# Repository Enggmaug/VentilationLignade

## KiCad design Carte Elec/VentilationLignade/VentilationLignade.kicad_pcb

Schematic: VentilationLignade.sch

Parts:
C1, C2, C3: 0.1uF; C_Rect_L7_W2.5_P5
C4, C5, C6, C7: 1uF; C_Radial_D8_L11.5_P3.5
P1: RelaisBoard1; Pin_Header_Straight_1x04
P2: PUIT_CAN; bornier2
P3: RelaisBoard2; Pin_Header_Straight_1x04
P4: TEMP_EXT; bornier2
P5: RelaisBoard3; Pin_Header_Straight_1x04
P6: TEMP_INT; bornier2
P7: RelaisBoard4; Pin_Header_Straight_1x04
P8: RelaisBoard5; Pin_Header_Straight_1x04
P9: TFT; Pin_Header_Straight_1x09
P10: SDCard; Pin_Header_Straight_1x05
P11: Codeur Rotatif; Pin_Header_Straight_1x05
P12: Teensy Bottom; Pin_Header_Straight_1x10
P13: EndStops1; bornier2
P14: Teensy_Haut; Pin_Header_Straight_1x13
P15: EndStops2; bornier2
P16: Teensy_cote; Pin_Header_Straight_1x07
P17: Retour 12V; bornier2
P18: Masse_12V; Pin_Header_Straight_1x04
P19, P20: CONN_01X03; Alim
P21: 12V_1et2; bornier2
P22: Teensy_Bas; Pin_Header_Straight_1x13
P23: Serial; Pin_Header_Straight_1x04
P24: CHEMINEE; bornier2
P25: RT_CLK1; Pin_Header_Straight_1x04
P26: RT_CLK2; Pin_Header_Straight_1x04
P27, P28, P29, P30: CONN_1; VIS
R1: R; Resistor_Horizontal_RM15mm
R2, R24, R26, R28: 4.47K; R_1206_HandSoldering
R3, R25, R27, R29: 91K; R_1206_HandSoldering
R30: 100K; R_1206_HandSoldering
RV1, RV2, RV3, RV4: 10K; Potar
SW2: BackLight_On/ff; Pin_Header_Straight_1x03

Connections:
12V1: P19.1, P21.1
12V1_ON: P7.3, P22.8
12V2: P20.1, P21.2 (PM)
12V2_ON: P8.3, P12.9
12V_CHECK: P14.1; also elsewhere on the board
+3.3V: C4.2, C5.2, C6.2, C7.2, P2.1, P4.1, P6.1, P9.1, P11.4, P14.11, P24.1, P25.3, R30.2; also elsewhere on the board
+5V: P1.4, P3.4, P5.4, P7.4, P8.4, P14.13, P23.4, SW2.1
/Optocouplers/12V_IN: P17.2 (PM); also elsewhere on the board
/Optocouplers/END_1_1: P13.2 (PM); also elsewhere on the board
/Optocouplers/END_1_2: P13.1; also elsewhere on the board
/Optocouplers/END_2_1: P15.2 (PM); also elsewhere on the board
/Optocouplers/END_2_2: P15.1; also elsewhere on the board
AGND: P14.12, RV1.1, RV2.1, RV3.1, RV4.1
BYPASS_1_F: P1.3, P22.2
BYPASS_1_O: P1.2, P22.3
BYPASS_2_F: P3.3, P22.4
BYPASS_2_O: P3.2, P22.5
ENCODEUR_A: C1.1, P11.1, P12.2
ENCODEUR_B: C2.1, P11.2, P12.3
ENCODEUR_SW: C3.1, P11.3, P12.4
ENDSTOP_1_1: P14.6; also elsewhere on the board
ENDSTOP_1_2: P14.5; also elsewhere on the board
ENDSTOP_2_1: P14.4; also elsewhere on the board
ENDSTOP_2_2: P14.3; also elsewhere on the board
GND: C1.2, C2.2, C3.2, P1.1, P3.1, P5.1, P7.1, P8.1, P9.2, P11.5, P16.4, P22.1, P23.1, P25.1, P25.2; also elsewhere on the board
GNDPWR: P17.1, P18.1, P18.2, P18.3, P18.4, P19.2, P19.3, P20.2, P20.3; also elsewhere on the board
unnamed: P9.4, R30.1
unnamed: P9.8, R1.1
unnamed: R1.2, SW2.2
unnamed: R2.2, R3.1
unnamed: R3.2, RV1.2, RV1.3
unnamed: R24.2, R25.1
unnamed: R25.2, RV2.2, RV2.3
unnamed: R26.2, R27.1
unnamed: R27.2, RV3.2, RV3.3
unnamed: R28.2, R29.1
unnamed: R29.2, RV4.2, RV4.3
RTCLK_CS: P22.11, P26.4
RTCLK_INTERRUPT: P22.10, P25.4
RX: P12.5, P23.2
SD_CS: P10.1, P14.2
SELECT_12V: P8.2, P12.1
SELECT_VMC: P7.2, P22.9
SPI_MISO: P9.9, P10.4, P16.1, P26.2
SPI_MOSI: P9.6, P10.2, P22.13, P26.3
SPI_SCK: P9.7, P10.3, P16.7, P26.1
TCHEM_AN: C7.1, P14.10, P24.2 (PM), R28.1
TEXT_AN: C5.1, P4.2 (PM), P14.8, R24.1
TFT_CS: P9.3, P22.12
TFT_DC: P9.5, P12.10
TFT_ONOFF: P12.8, SW2.3
TINT_AN: C6.1, P6.2 (PM), P14.7, R26.1
TPUIT_AN: C4.1, P2.2 (PM), P14.9, R2.1
TX: P12.6, P23.3
VENT_CAVE: P5.3, P22.6
VENT_CHEMINEE: P5.2, P22.7

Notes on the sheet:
Vis
VERS RELAIS
Entrées 12V
Vers RELAIS
CODEUR ROTATIF
ECRAN TFT
FINS DE COURSE BYPASS
TEENSY 3.1
RETOUR 12V
POWER FLAGS
REAL TIME CLOCK

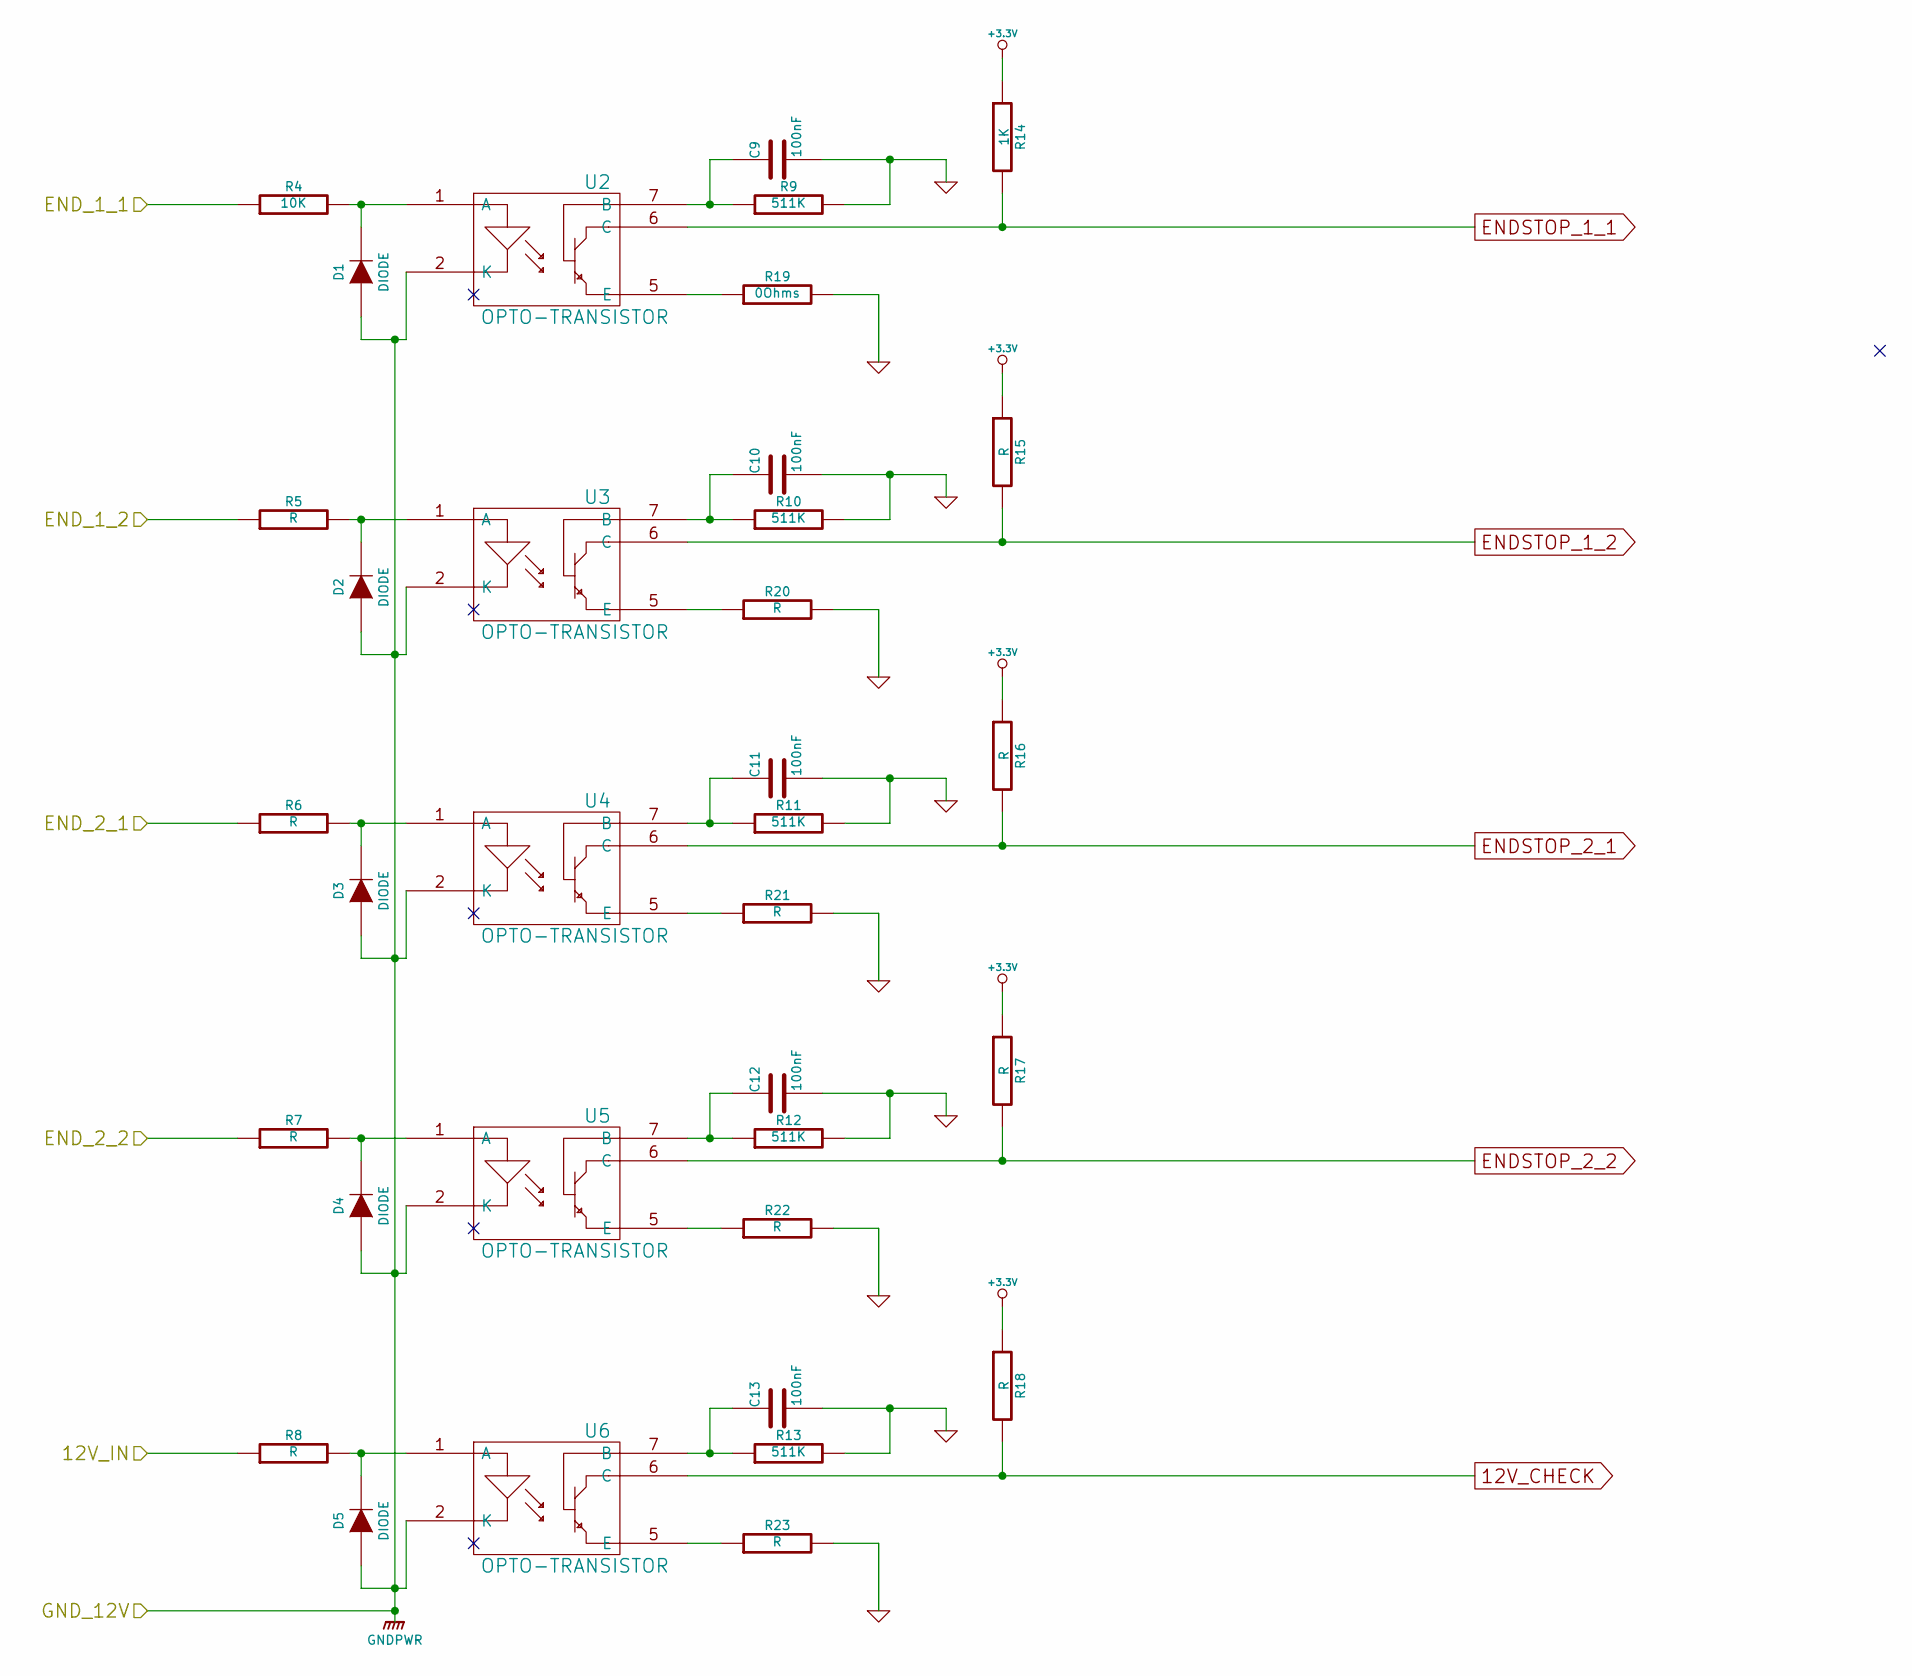
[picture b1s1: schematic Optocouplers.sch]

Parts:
C9, C10, C11, C12, C13: 100nF; C_0805_HandSoldering
D1, D2, D3, D4, D5: DIODE; SOT-23
R4: 10K; R_1206_HandSoldering
R5, R6, R7, R8, R15, R16, R17, R18, R20, R21, R22, R23: R; R_1206_HandSoldering
R9, R10, R11, R12, R13: 511K; R_1206_HandSoldering
R14: 1K; R_1206_HandSoldering
R19: 0Ohms; R_1206_HandSoldering
U2, U3, U4, U5, U6: OPTO-TRANSISTOR; SOIC-8-N

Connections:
12V_CHECK: R18.2, U6.6 (C); also elsewhere on the board
+3.3V: R14.1, R15.1, R16.1, R17.1, R18.1; also elsewhere on the board
/Optocouplers/12V_IN: R8.1; also elsewhere on the board
/Optocouplers/END_1_1: R4.1; also elsewhere on the board
/Optocouplers/END_1_2: R5.1; also elsewhere on the board
/Optocouplers/END_2_1: R6.1; also elsewhere on the board
/Optocouplers/END_2_2: R7.1; also elsewhere on the board
ENDSTOP_1_1: R14.2, U2.6 (C); also elsewhere on the board
ENDSTOP_1_2: R15.2, U3.6 (C); also elsewhere on the board
ENDSTOP_2_1: R16.2, U4.6 (C); also elsewhere on the board
ENDSTOP_2_2: R17.2, U5.6 (C); also elsewhere on the board
GND: C9.2, C10.2, C11.2, C12.2, C13.2, R9.2, R10.2, R11.2, R12.2, R13.2, R19.2, R20.2, R21.2, R22.2, R23.2; also elsewhere on the board
GNDPWR: D1.1 (A), D2.1 (A), D3.1 (A), D4.1 (A), D5.1 (A), U2.2 (K), U3.2 (K), U4.2 (K), U5.2 (K), U6.2 (K); also elsewhere on the board
unnamed: C9.1, R9.1, U2.7 (B)
unnamed: C10.1, R10.1, U3.7 (B)
unnamed: C11.1, R11.1, U4.7 (B)
unnamed: C12.1, R12.1, U5.7 (B)
unnamed: C13.1, R13.1, U6.7 (B)
unnamed: D1.2 (K), R4.2, U2.1 (A)
unnamed: D2.2 (K), R5.2, U3.1 (A)
unnamed: D3.2 (K), R6.2, U4.1 (A)
unnamed: D4.2 (K), R7.2, U5.1 (A)
unnamed: D5.2 (K), R8.2, U6.1 (A)
unnamed: R19.1, U2.5 (E)
unnamed: R20.1, U3.5 (E)
unnamed: R21.1, U4.5 (E)
unnamed: R22.1, U5.5 (E)
unnamed: R23.1, U6.5 (E)

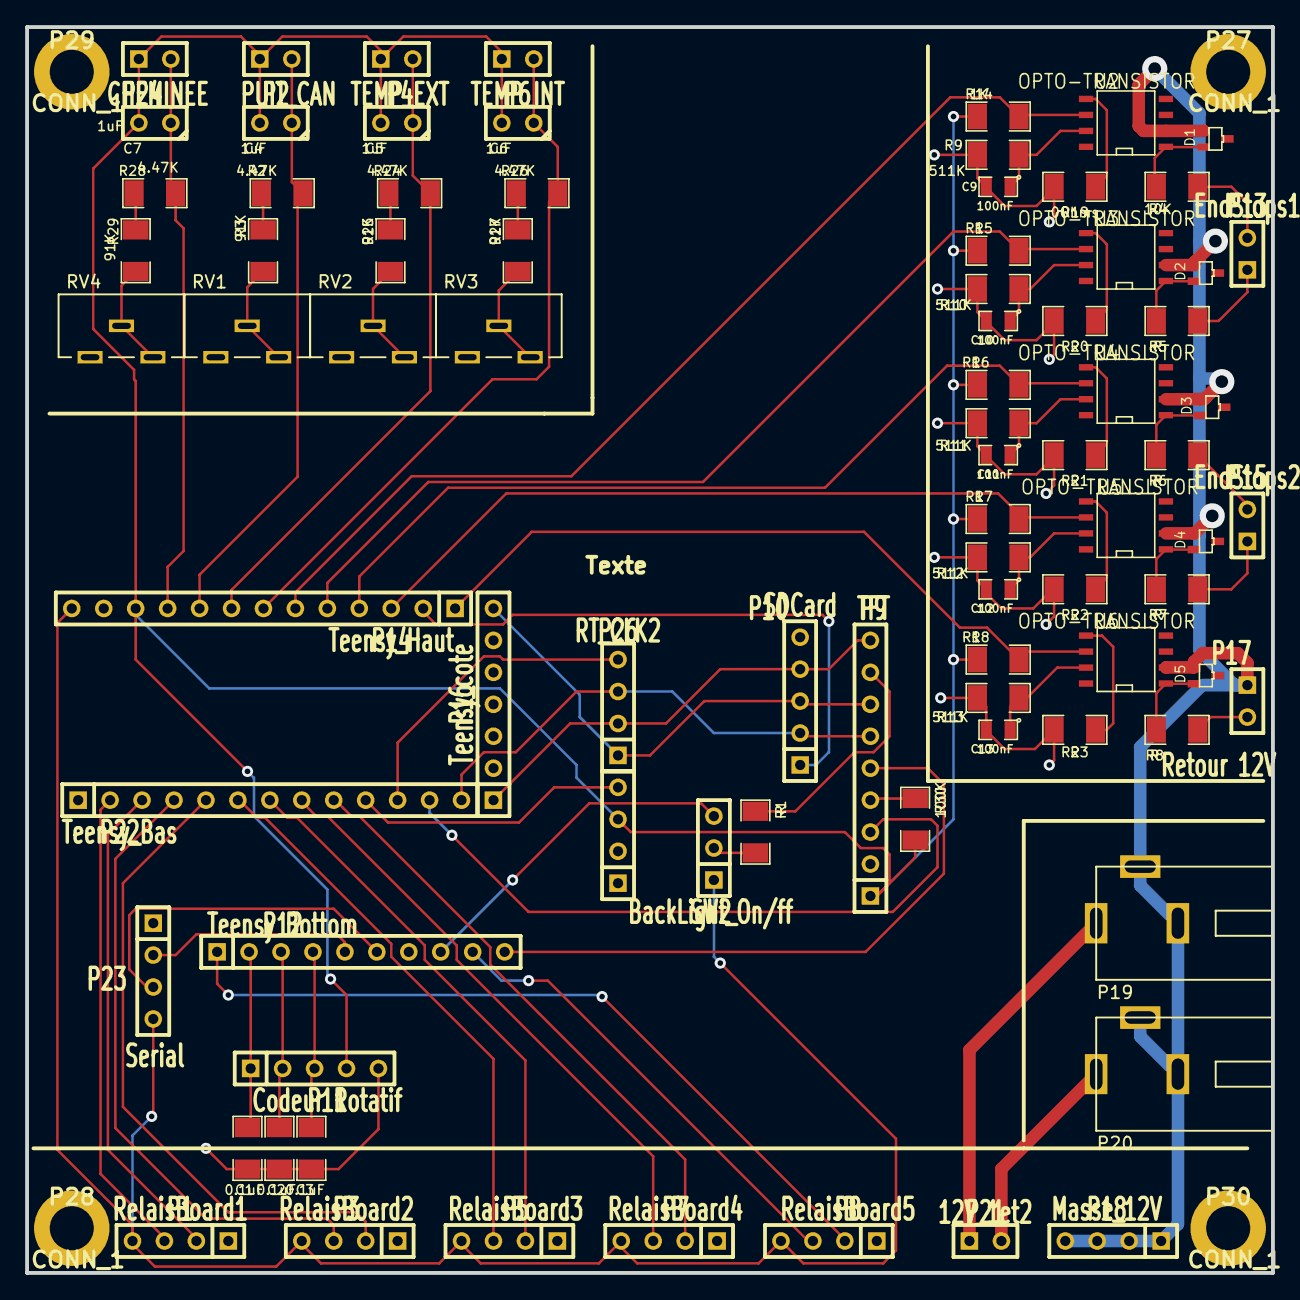
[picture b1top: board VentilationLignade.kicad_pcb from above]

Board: 2 copper layers, 99.1 x 99.1 mm, 86 parts (0 on the bottom side), 70 nets.

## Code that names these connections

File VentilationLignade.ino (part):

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#define TEMP_SAMPLES_NB 10

//DEFINE des Numeros de Pins
#define BYPASS_1_F     0
#define BYPASS_1_O     1
#define BYPASS_2_F     2
#define BYPASS_2_O     3
#define VENT_CAVE      4
#define VENT_CHEM      5
#define V12_1_ON       6
#define SELECT_VMC     7
#define RTCLK_INT      8
#define RTCLK_CS       9
#define TFT_CS         10
#define SPI_MOSI       11
#define SPI_MISO       12
#define SPI_CLK        13
#define CHECK_12V      14
#define SDCARD_CS      15
#define ENDSTOP_2_2    16
#define ENDSTOP_2_1    17
#define ENDSTOP_1_2    18
#define ENDSTOP_1_1    19
#define T_INT          20
#define T_EXT          21
#define T_PUIT         22
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#define COD_SW         25
#define TX_SPARE       26
#define TFT_ON         27
#define TFT_DC         28
#define V12_2_ON       29
#define SPARE          30
#define RX_SPARE       31
#define COD_DT         32
#define SELECT_12V     33 
#define TFT_RST        -1


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
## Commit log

2015-08-16 Ajout des fichiers courants
2015-08-18 Definition des transitions de la machine d'etat. Ecriture de la trame de fond.
2015-08-18 Ajout du fichier excel de définition
2015-08-18 Nettoyage, sortie de la selection VMC des ventilos
2015-08-18 Ajout Mode Maintenance, Codage de la machine d'états
2015-08-18 Debug des define des endstops.
2015-08-21 Version Opérationelle 1.0
2015-08-21 Affichage des commandes envoyées par Serie.
2015-08-21 Amelioration des messages de debug
2015-08-21 Ajout Excel Branchements
2015-08-21 Correction Bug : Eteindre l'alim en fin de Bypass2
2015-08-21 Changement des pins pour V12 nb 2
2015-08-23 Debug en place - Attention Pb d'initialisation
2015-08-23 Reprise totale de la structure de code
2015-08-23 Corrections sur cible. Programme fonctionnel en mode MAINTENANCE
2015-08-24 Changement des valeurs d'états. La machine d'états est retirée de la documentation, car obsolete vis à vis du code.
2015-08-24 Mise à jour des branchements.
2015-08-24 Modifications suite aux tests sur cible en mode NORMAL.
2015-09-02 reaffectation des Pins pour mettre en place écran et SDCard en SPI.
    Puisqu'il manque des IOs, on prévoit un controleur d'IO en I2C.
2015-09-02 Ajout de commentaires
2015-09-02 Ajout d'un affichage de test sur écran TFT
2015-09-02 Ajout des différents écrans à afficher.
2015-09-02 Implementation en cours de l'ecran.
2015-09-02 Ecran Fonctionnel sur Teensy 3.1 - a essayer sur Teensy LC
2015-09-05 Ajout d'écrans faits sur Photoshop. Décrivent les entrées seulement. Les sorties doivent rester en mode texte pour le moment (compliqué de représenter les VMCs)
2015-09-05 1er Essai bof bof : Probleme l'affichage est super lent, et la SD card n'est pas reconnue.
2015-09-05 Intégration des écrans BMP sur lecture carte SD.
2015-09-06 Separation en fichiers pour chaque partie, et ajout de thilam pour le message d'attente
2015-09-06 Reprise complete du Pinning pour etre capable d'accepter un encodeur en plus, et en utilisant un Teensy 3.1 au lieu de LC.
2015-09-06 Ajout du projet KiCad pour Imprimer une carte qui va bien.
2015-09-06 Ajout Netliste creation Board
2015-09-07 Dessin de carte. Changement des pins pour avoir un truc cohérent au niveau de la carte.
2015-09-08 Ajout d'un RS232 MAX au cas ou.
2015-09-09 Reprise de la carte => Dimensions réduites 50x100mm
2015-09-13 Reprise de carte : Suppression MAX232, pour avoir la place de mettre les MOC207
2015-09-13 Changement taille 100x160 (pour fab maison)
2015-09-14 Traceage Poscript
2015-09-15 Agrandissement des pads de connecteur, pour pouvoir percer et souder sans soucis.
2015-09-15 Eloignement des pistes proches
2015-09-16 Renommage des Températures
2015-10-02 Modification carte pour utiliser thermistors et real time clock.
2015-10-04 Correction des zones sur le dessus.
2015-10-08 Ajout des placements de perçages sur les pastilles
2015-11-12 Modif pour ouvrir sur Kicad last version
2015-11-13 Changement des boitiers en cours de reroutage
2015-11-13 Ajout de l alib rescue (cree lors du passage a la derniere version de kicad ?)
2015-11-14 Ajout de valeur de composants
2015-11-17 Ajout des modèles 3D
2016-07-17 Réintégration du projet "TestMenu"
2016-07-25 Changement de pin suite a soudure
2016-07-27 Ajout de la lecture des températures - part 1
2016-07-27 Ajout de la lecture des températures - part 2 - ok
2016-07-27 Incrementation du compteur de moyenne floatante sur les températures
2016-07-27 Ajout de la détection de changement d'état d'entrée
2016-07-27 Le seuil de température extérieure basse n'est pas réglable : il s'agit de la température du puit Canandien. Les seuils et hysteresis du PC ne sont pas réglables : aucune sortie ne lui est lié.
2016-07-27 Début de la mise en place des sorties
2016-07-28 Implementation des gestion de sorties + ecran associé
2016-07-28 Ajout de la gestion du Debug : On peut modifier la température à la main.
2016-07-28 Si on quitte le mode debug, on reprend les températures réelles.
2016-07-30 Ajout du fichier de gestion des sorties, et corrections liées au menu de maintenance.
2016-07-30 Correction de Bugs Maintenance
2016-07-31 Essais avec Problèmes
2016-08-28 Indication de la suppression de seuil TExt Basse dans le fichier xls
2016-08-28 Reorder des temperatures
2017-04-06 Carte a reprendre
2017-04-09 Modif de la carte => Commande SEEED !!!
2017-06-05 Fichiers en cours sur mon PC
2017-06-05 Modif elec et dossier de commande carte
2017-06-25 Premières modifs pour faire tourner la carte Imprimée Seeed
2023-08-12 Home Assistant : ESP Home
